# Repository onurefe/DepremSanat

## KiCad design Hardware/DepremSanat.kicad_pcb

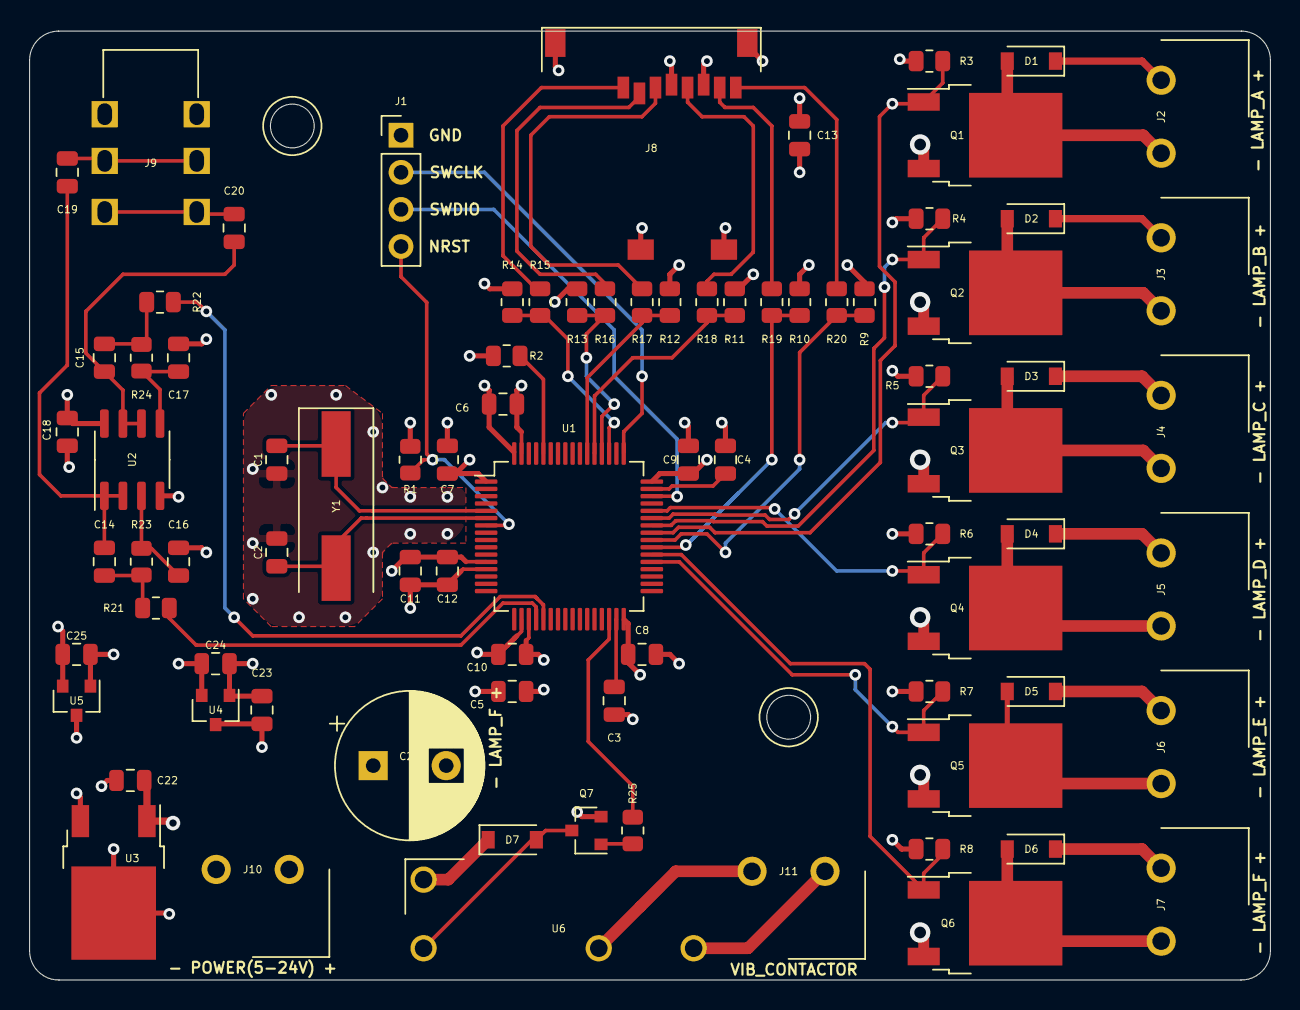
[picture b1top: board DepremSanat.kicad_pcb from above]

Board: 4 copper layers, 85.0 x 65.0 mm, 82 parts (0 on the bottom side), 52 nets.

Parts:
C1, C2: 18p; C_0805_2012Metric
C3, C4, C5, C11, C19, C20, C23, C24, C25: 4.7u; C_0805_2012Metric
C6, C7, C8, C9, C10, C12, C13, C18: 100n; C_0805_2012Metric
C14, C15: 1.8n; C_0805_2012Metric
C16, C17: 1n; C_0805_2012Metric
C21: 1000u 35v; CP_Radial_D10.0mm_P5.00mm
C22: 4.7u 25v; C_0805_2012Metric
D1, D2, D3, D4, D5, D6, D7: 1N4148W-HT; D_SOD-123
J1: Conn_01x04_Male; PinHeader_1x04_P2.54mm_Vertical
J2, J3, J4, J5, J6, J7, J10, J11: Screw_Terminal_01x02; DG130-5.0-02P-14-00SH
J8: Wurth_693071010811
J9: Audio jack; L-KLS1-TSJ3.5-009C
Q1, Q2, Q3, Q4, Q5, Q6: P16B6SB-5071; TO-252-2
Q7: MMBT3904-HT; SOT-23
R1, R2, R9, R10, R11, R12, R13, R14, R21, R22: 10k; R_0805_2012Metric
R3, R4, R5, R6, R7, R8, R25: 1k; R_0805_2012Metric
R15, R16, R17, R18, R19, R20: 27R; R_0805_2012Metric
R23, R24: 13k; R_0805_2012Metric
U1: STM32F405RGTx; LQFP-64_10x10mm_P0.5mm
U2: AD8602; SOIC-8_3.9x4.9mm_P1.27mm
U3: MC78M05_TO252; TO-252-2
U4, U5: AP2210; SOT-23
U6: ALDP112W
Y1: 8MHz; Crystal_SMD_HC49-SD

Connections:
+5V: C23.2, R3.1, R4.1, R5.1, R6.1, R7.1, R8.1, U3.3, U4.3, U5.3
+12V: C21.1, C22.1, D1.1, D2.1, D3.1, D4.1, D5.1, D6.1, D7.1, J2.1, J3.1, J4.1, J5.1, J6.1, J7.1, J10.1, U3.1, U6.1
/Audio/AUDIO_CH0: R21.2, U1.20
/Audio/AUDIO_CH1: R22.2, U1.21
/LampControl/LAMP_A_CTRL: Q1.1, R3.2, U1.41
/LampControl/LAMP_A_LSIDE: D1.2, J2.2, Q1.2
/LampControl/LAMP_B_CTRL: Q2.1, R4.2, U1.42
/LampControl/LAMP_B_LSIDE: D2.2, J3.2, Q2.2
/LampControl/LAMP_C_CTRL: Q3.1, R5.2, U1.43
/LampControl/LAMP_C_LSIDE: D3.2, J4.2, Q3.2
/LampControl/LAMP_D_CTRL: Q4.1, R6.2, U1.44
/LampControl/LAMP_D_LSIDE: D4.2, J5.2, Q4.2
/LampControl/LAMP_E_CTRL: Q5.1, R7.2, U1.37
/LampControl/LAMP_E_LSIDE: D5.2, J6.2, Q5.2
/LampControl/LAMP_F_CTRL: Q6.1, R8.2, U1.38
/LampControl/LAMP_F_LSIDE: D6.2, J7.2, Q6.2
/MCU/NRST: J1.4, R1.1, U1.7
/MCU/SD_CLK: R11.1, R18.2, U1.53
/MCU/SD_CMD: R12.1, R17.2, U1.54
/MCU/SD_D0: R10.1, R19.2, U1.39
/MCU/SD_D1: R9.1, R20.2, U1.40
/MCU/SD_D2: R14.1, R15.2, U1.51
/MCU/SD_D3: R13.1, R16.2, U1.52
/MCU/SWCLK: J1.2, U1.49
/MCU/SWDIO: J1.3, U1.46
/MCU/VIBRATION_CTRL: R25.2, U1.30
/Vibration/VIBRATION_A: J11.1, U6.2
/Vibration/VIBRATION_B: J11.2, U6.3
GND: C1.2, C2.2, C3.2, C4.2, C5.2, C6.2, C7.2, C8.2, C9.2, C10.2, C11.2, C12.1, C13.1, C16.2, C17.2, C18.2, C21.2, C22.2, C23.1, C24.2, C25.2, J1.1, J8.6, J8.9, J9.1, J10.2, Q1.3, Q2.3, Q3.3, Q4.3, Q5.3, Q6.3, Q7.2, R2.2, U1.12, U1.18, U1.63, U2.4, U3.2, U4.1, U5.1
unnamed: C1.1, U1.5, Y1.1
unnamed: C2.1, U1.6, Y1.2
unnamed: C3.1, U1.31
unnamed: C4.1, U1.47
unnamed: C14.1, C19.2, U2.1, U2.2
unnamed: C14.2, R21.1, R23.2
unnamed: C15.1, C20.2, U2.6, U2.7
unnamed: C15.2, R22.1, R24.2
unnamed: C16.1, R23.1, U2.3
unnamed: C17.1, R24.1, U2.5
unnamed: C19.1, J9.2
unnamed: C20.1, J9.3
unnamed: D7.2, Q7.3, U6.4
unnamed: J8.1, R15.1
unnamed: J8.2, R16.1
unnamed: J8.3, R17.1
unnamed: J8.5, R18.1
unnamed: J8.7, R19.1
unnamed: J8.8, R20.1
unnamed: Q7.1, R25.1
unnamed: R2.1, U1.60
VDD: C5.1, C6.1, C7.1, C8.1, C9.1, C10.1, C13.2, C24.1, J8.4, R1.2, R9.2, R10.2, R11.2, R12.2, R13.2, R14.2, U1.1, U1.19, U1.32, U1.48, U1.64, U4.2
VDDA: C11.1, C12.2, C18.1, C25.1, U1.13, U2.8, U5.2

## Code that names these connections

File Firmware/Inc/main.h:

/* USER CODE BEGIN Header */
/**
  ******************************************************************************
  * @file           : main.h
  * @brief          : Header for main.c file.
  *                   This file contains the common defines of the application.
  ******************************************************************************
  * @attention
  *
  * <h2><center>&copy; Copyright (c) 2021 STMicroelectronics.
  * All rights reserved.</center></h2>
  *
  * This software component is licensed by ST under Ultimate Liberty license
  * SLA0044, the "License"; You may not use this file except in compliance with
  * the License. You may obtain a copy of the License at:
  *                             www.st.com/SLA0044
  *
  ******************************************************************************
  */
/* USER CODE END Header */

/* Define to prevent recursive inclusion -------------------------------------*/
#ifndef __MAIN_H
#define __MAIN_H

#ifdef __cplusplus
extern "C" {
#endif

/* Includes ------------------------------------------------------------------*/
#include "stm32f2xx_hal.h"

/* Private includes ----------------------------------------------------------*/
/* USER CODE BEGIN Includes */

/* USER CODE END Includes */

/* Exported types ------------------------------------------------------------*/
/* USER CODE BEGIN ET */

/* USER CODE END ET */

/* Exported constants --------------------------------------------------------*/
/* USER CODE BEGIN EC */

/* USER CODE END EC */

/* Exported macro ------------------------------------------------------------*/
/* USER CODE BEGIN EM */

/* USER CODE END EM */

void HAL_TIM_MspPostInit(TIM_HandleTypeDef *htim);

/* Exported functions prototypes ---------------------------------------------*/
void Error_Handler(void);

/* USER CODE BEGIN EFP */

/* USER CODE END EFP */

/* Private defines -----------------------------------------------------------*/
#define POWER_ELEMENTS_SAMPLING_FREQ 64
#define TIM6_RELOAD (((TIM6_CLOCK_FREQ/(TIM6_PRESCALER+1))/AUDIO_SAMPLING_FREQ)-1)
#define TIM6_CLOCK_FREQ 60000000
#define AUDIO_SAMPLING_FREQ 4096
#define TIM1_RELOAD (((TIM1_CLOCK_FREQ/(TIM1_PRESCALER+1))/POWER_ELEMENTS_SAMPLING_FREQ)-1)
#define TIM6_PRESCALER 0
#define TIM1_CLOCK_FREQ 60000000
#define TIM1_PRESCALER 59
#define TIM3_CLOCK_FREQ 60000000
#define TIM3_RELOAD (((TIM3_CLOCK_FREQ/(TIM3_PRESCALER+1))/POWER_ELEMENTS_SAMPLING_FREQ)-1)
#define TIM3_PRESCALER 59
#define VOID_CARD_DETECT_Pin GPIO_PIN_1
#define VOID_CARD_DETECT_GPIO_Port GPIOA
#define VIBRATION_CTRL_Pin GPIO_PIN_11
#define VIBRATION_CTRL_GPIO_Port GPIOB
#define LAMP_E_CTRL_Pin GPIO_PIN_6
#define LAMP_E_CTRL_GPIO_Port GPIOC
#define LAMP_F_CTRL_Pin GPIO_PIN_7
#define LAMP_F_CTRL_GPIO_Port GPIOC
#define LAMP_A_CTRL_Pin GPIO_PIN_8
#define LAMP_A_CTRL_GPIO_Port GPIOA
#define LAMP_B_CTRL_Pin GPIO_PIN_9
#define LAMP_B_CTRL_GPIO_Port GPIOA
#define LAMP_C_CTRL_Pin GPIO_PIN_10
#define LAMP_C_CTRL_GPIO_Port GPIOA
#define LAMP_D_CTRL_Pin GPIO_PIN_11
#define LAMP_D_CTRL_GPIO_Port GPIOA
/* USER CODE BEGIN Private defines */

/* USER CODE END Private defines */

#ifdef __cplusplus
}
#endif

#endif /* __MAIN_H */

/************************ (C) COPYRIGHT STMicroelectronics *****END OF FILE****/

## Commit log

2021-09-15 DepremSanat v1.0
    Hardware, firmware and software components are working.
2021-09-17 Improvisations of notebook file.
    DONE:
    +Station file not needed to be seperately downloaded.
    +Flexible time window can be selected for noise sample.
    TO DO:
    +Sampling rate can be done more flexible on the hardware side.
    +Different "real" stations can be used for driving lamps.
2021-09-19 Merging option of the processed file with the background sound.
